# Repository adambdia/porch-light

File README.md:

# Porch Light Controller

My porch light drifts over time, getting out of sync. Probably because it's old. This is my attempt to IOT-ify it.

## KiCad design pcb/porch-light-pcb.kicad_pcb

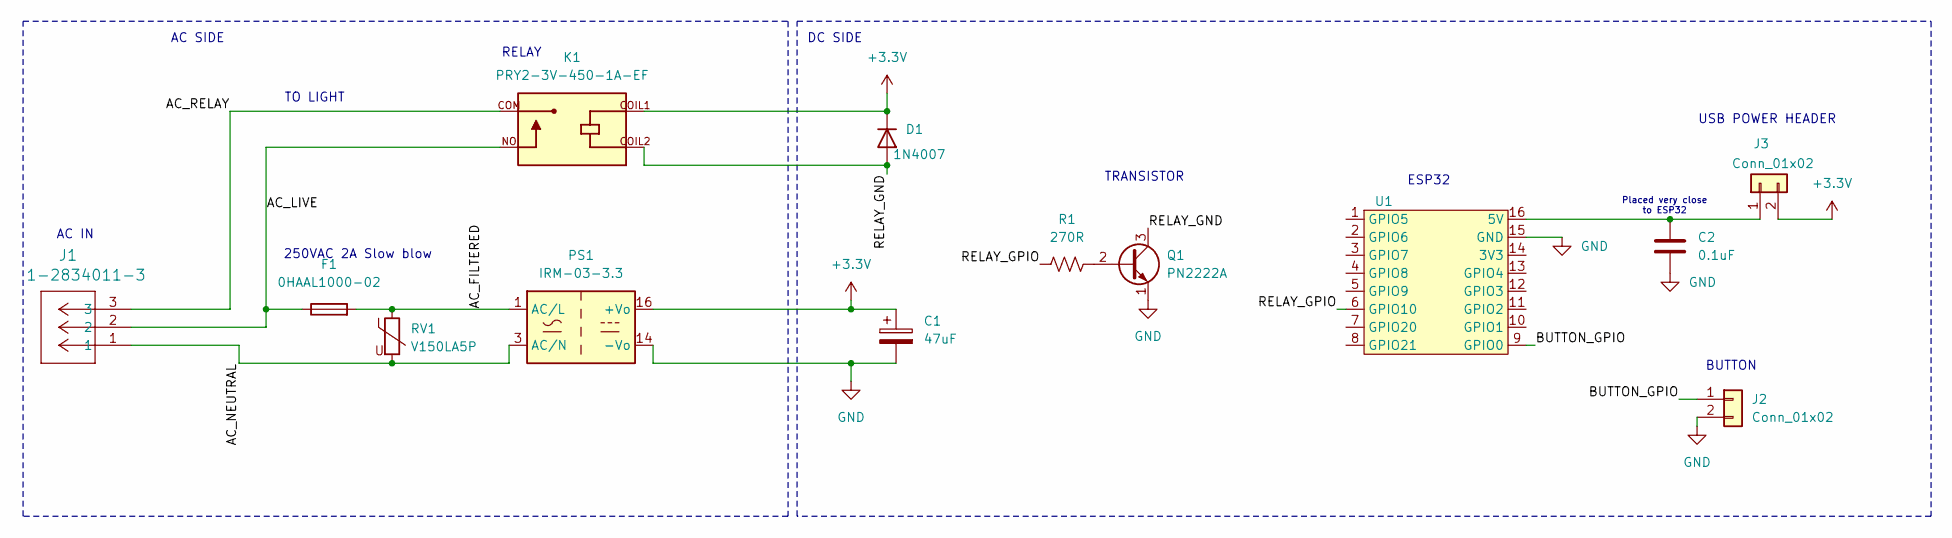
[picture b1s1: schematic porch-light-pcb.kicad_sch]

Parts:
C1: 47uF; CP_Radial_D4.0mm_P1.50mm
C2: 0.1uF; C_0603_1608Metric_Pad1.08x0.95mm_HandSolder
D1: 1N4007; D_SOD-123F
F1: 0HAAL1000-02; FUSRR508W60L840T400H810B
J1: 1-2834011-3; CONN_1-2834011-3_TEC
J2, J3: Conn_01x02; PinHeader_1x02_P2.54mm_Vertical
K1: PRY2-3V-450-1A-EF; RELAY_PRY2-3V-450-1A-EF; PARTREV 1.0
PS1: IRM-03-3.3; Converter_ACDC_MeanWell_IRM-03-xx_THT
Q1: PN2222A; TO-92_Inline
R1: 270R; R_Axial_DIN0207_L6.3mm_D2.5mm_P10.16mm_Horizontal
RV1: V150LA5P; RV_Disc_D12mm_W5.8mm_P7.5mm
U1: TENSTAR_ESP32-C3-SUPERMINI

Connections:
+3.3V: C1.1, D1.1 (K), J3.2, K1.COIL1, PS1.16 (+Vo)
/AC_FILTERED: F1.2, PS1.1 (AC/L), RV1.1
/AC_LIVE: F1.1, J1.2, K1.NO
/AC_NEUTRAL: J1.1, PS1.3 (AC/N), RV1.2
/AC_RELAY: J1.3, K1.COM
/BUTTON_GPIO: J2.1, U1.9 (GPIO0)
/RELAY_GND: D1.2 (A), K1.COIL2, Q1.3 (C)
/RELAY_GPIO: R1.1, U1.6 (GPIO10)
GND: C1.2, C2.1, J2.2, PS1.14 (-Vo), Q1.1 (E), U1.15 (GND)
unnamed: C2.2, J3.1, U1.16 (5V)
unnamed: Q1.2 (B), R1.2

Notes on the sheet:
RELAY
Placed very close to ESP32
TO LIGHT
DC SIDE
USB POWER HEADER
TRANSISTOR
AC SIDE
250VAC 2A Slow blow
ESP32
AC IN
BUTTON

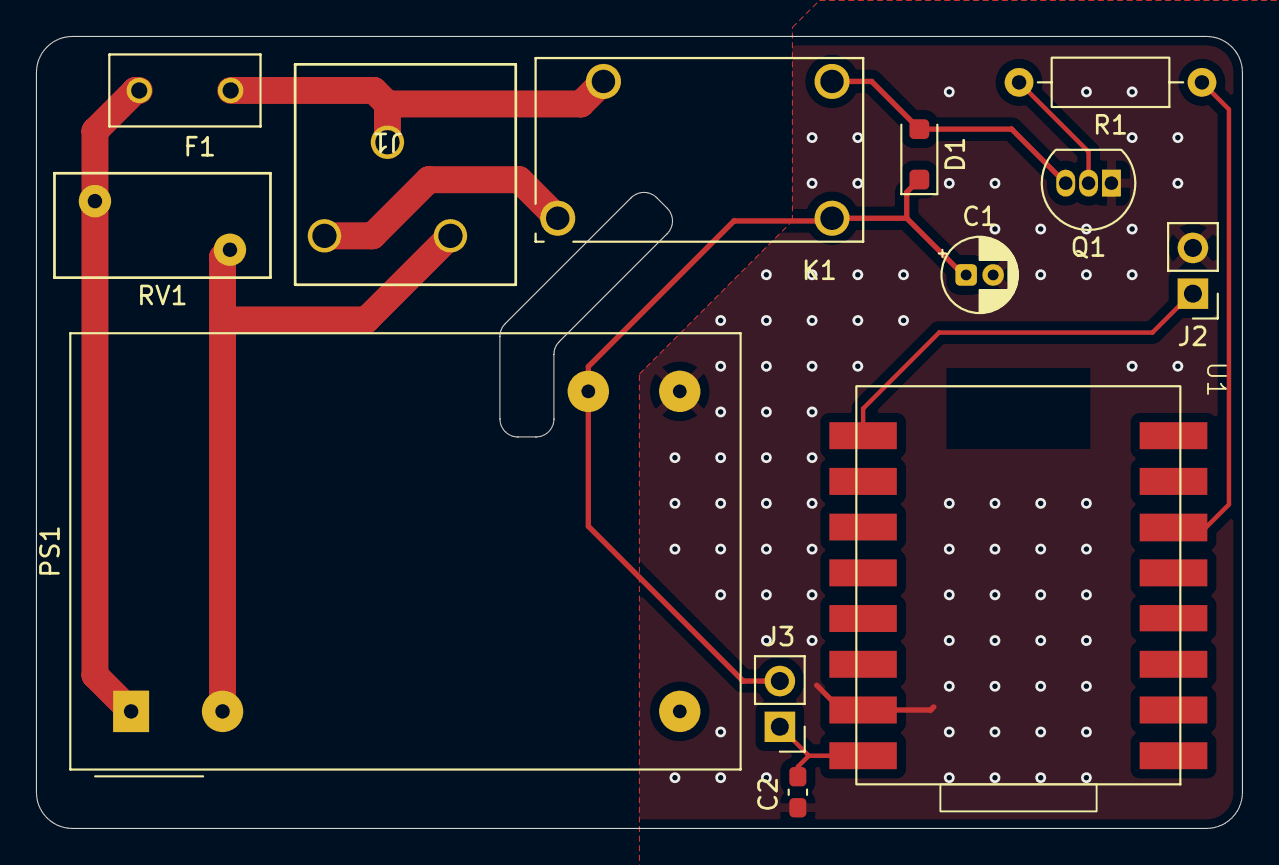
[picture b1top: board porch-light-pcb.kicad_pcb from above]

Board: 2 copper layers, 67.0 x 44.0 mm, 13 parts (0 on the bottom side), 11 nets.
